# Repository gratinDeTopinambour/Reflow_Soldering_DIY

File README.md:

# Reflow Soldering DIY Controller

**Convert a standard consumer oven into a precise PCB reflow soldering station.**

This repository contains the complete electronics design, firmware, and mechanical files for a custom Reflow Oven Controller.The device is designed to precisely control a resistive heating element to follow the specific temperature profiles required for SMD soldering.

---

## 📂 Repository Structure

* **`Code/`**: Firmware source code for the STM32C0 microcontroller.
* **`Doc/`**: General project documentation and datasheets.
* **`Electronics/`**: Hardware design files, including the detailed technical rationale.
* **`3Dprint/`**: STL and CAD files for the controller enclosure.

---

## ⚡ System Overview

The controller operates as a closed-loop feedback system that regulates the temperature of a resistive heating element. 

### Key Technical Features
* **Power Control**: Designed for 220V / 50Hz mains up to **2400W** (12A design reference).
* **Switching Strategy**: Utilizes Zero-Crossing control to minimize EMI and power losses.
* **Galvanic Isolation**: Complete isolation between high-voltage AC and low-voltage logic via an Opto-TRIAC.
* **Microcontroller**: Powered by an **STM32C0 series** ARM Cortex-M0+.
* **User Interface**: Features an OLED display (128x64) and a 6-button navigation cluster.
* **Thermal Sensing**: Uses a glass-encapsulated NTC thermistor rated up to **300°C**.

---

## 🛠️ Hardware Specifications

The hardware design prioritizes low-cost, hand-solderable components and robust thermal management.

### Power Stage
| Component | Selection | Rationale |
| :--- | :--- | :--- |
| **TRIAC** | BTA16-600CW | 16A max current, snubberless design  |
| **Opto-TRIAC** | MOC3063M | Zero-crossing detection and safe isolation  |
| **Heatsink** | Boyd 530002B02500G | $2.6^{\circ}C/W$ resistance to handle ~13W dissipation  |

### Logic & Power
* **Input**: USB-C (5V).
* **Regulation**: L1117S33 LDO (SOT-223) provides a stable 3.3V rail for the MCU.
* **Optimization**: The temperature sensor uses an optimized $1.8k\Omega$ bridge resistor to maximize ADC voltage swing between $60^{\circ}C$ and $260^{\circ}C$.

---

## 🚀 Installation & Safety

### ⚠️ WARNING: High Voltage
This project involves **220V AC Mains**. Fatal injury or fire can occur if handled incorrectly. 
* Always ensure the device is unplugged before touching the electronics.
* Ensure the TRIAC heatsink is properly mounted as temperatures can reach $\approx 100^{\circ}C$ during operation.

### Setup
1. **Assembly**: Refer to the schematics in `Electronics/`. The design uses TSSOP-20 and SOT-223 packages for easy manual assembly.
2. **Firmware**: Flash the STM32C0 via the SWD interface pins (PA14/PA15).
3. **Calibration**: The system is tuned for a standard NTC thermistor (NRBG105F3950B1F).

---

## 👤 Author
**Valentin LEFEBVRE** (@topinambour)  
*Document Date: 06/02/2026*

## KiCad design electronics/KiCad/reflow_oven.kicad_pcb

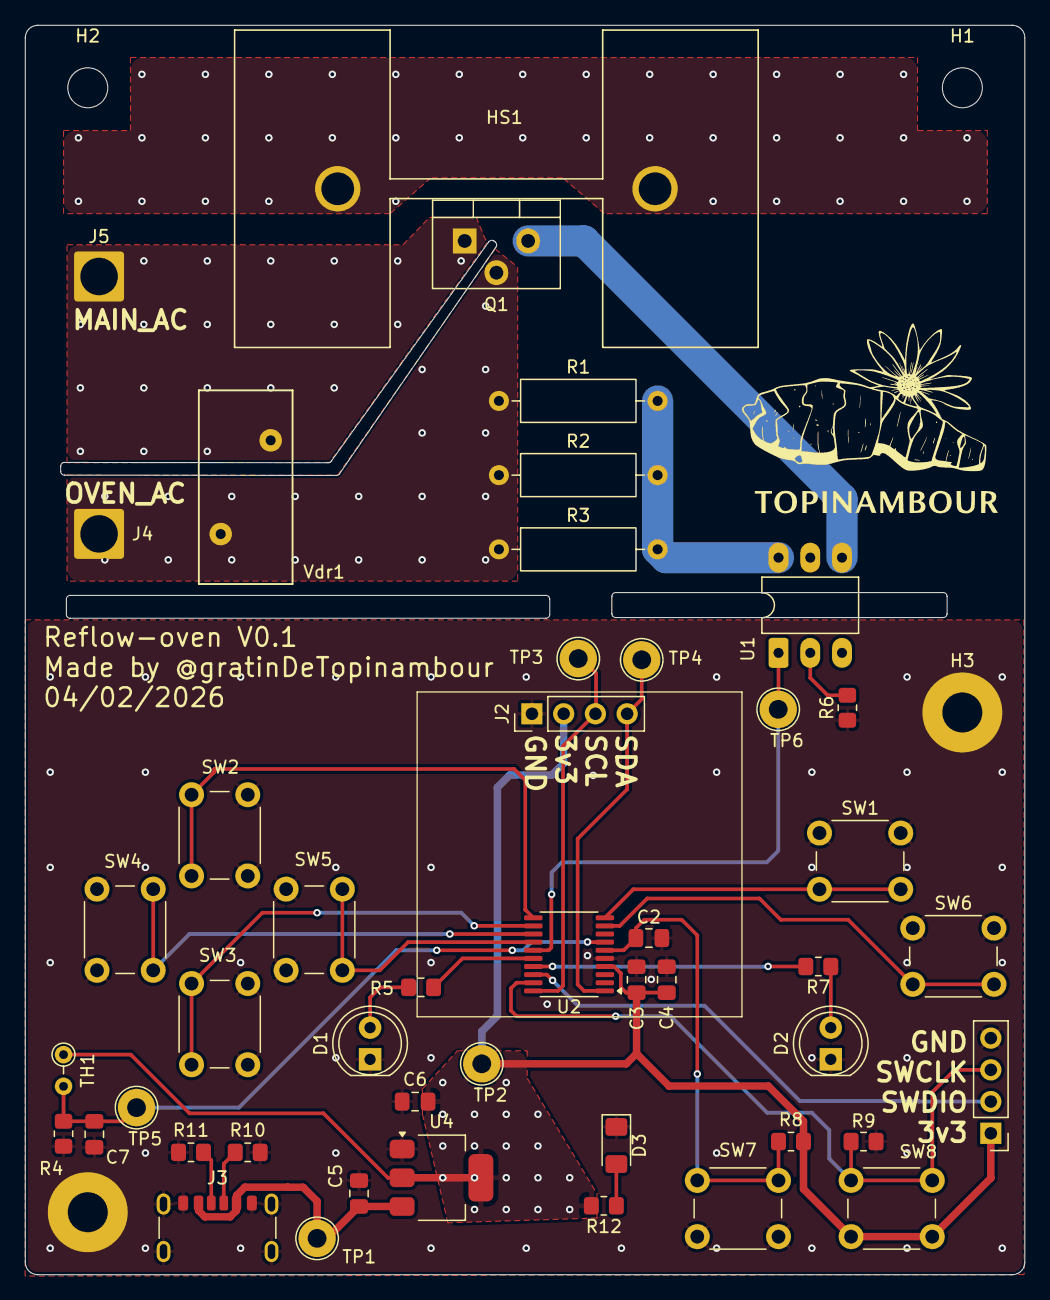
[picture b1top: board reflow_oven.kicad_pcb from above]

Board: 2 copper layers, 80.0 x 100.0 mm, 51 parts (0 on the bottom side), 29 nets.

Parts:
C2, C3, C7: 100nF; C_0805_2012Metric_Pad1.18x1.45mm_HandSolder
C4: 4.7uF; C_0805_2012Metric_Pad1.18x1.45mm_HandSolder
C5, C6: 10uF; C_0805_2012Metric_Pad1.18x1.45mm_HandSolder
D1: RED_LED; LED_D5.0mm
D2: GREEN_LED; LED_D5.0mm
D3: POWER_LED; LED_1206_3216Metric_Pad1.42x1.75mm_HandSolder
H1, H2: MountingHole; MountingHole_3.2mm_M3
H3, H4: MountingHole_Pad; MountingHole_3.2mm_M3_Pad
HS1: Heatsink; HEATSINK_530002B02500G
J1: Conn_01x04_Pin; PinHeader_1x04_P2.54mm_Vertical
J2: OLED_Display; PinHeader_1x04_P2.54mm_Vertical
J3: USB_C_Receptacle_PowerOnly_6P; USB_C_Receptacle_GCT_USB4125-xx-x-0190_6P_TopMnt_Horizontal
J4: Load_AC; SolderWire-2.5sqmm_1x01_D2.4mm_OD3.6mm
J5: Main_AC; SolderWire-2.5sqmm_1x01_D2.4mm_OD3.6mm
Q1: BTA16-600CW; TO-220-3_Vertical
R1, R2, R3: 1100; R_Axial_DIN0309_L9.0mm_D3.2mm_P12.70mm_Horizontal
R4: 1800; R_0805_2012Metric_Pad1.20x1.40mm_HandSolder
R5, R6, R7, R12: 150; R_0805_2012Metric_Pad1.20x1.40mm_HandSolder
R8, R9: 10k; R_0805_2012Metric_Pad1.20x1.40mm_HandSolder
R10, R11: 5.1k; R_0805_2012Metric_Pad1.20x1.40mm_HandSolder
SW1: Valid; SW_PUSH_6mm_H5mm
SW2: Up; SW_PUSH_6mm_H5mm
SW3: Down; SW_PUSH_6mm_H5mm
SW4: Left; SW_PUSH_6mm_H5mm
SW5: Right; SW_PUSH_6mm_H5mm
SW6: return; SW_PUSH_6mm_H5mm
SW7: NRST; SW_PUSH_6mm_H5mm
SW8: BOOT0; SW_PUSH_6mm_H5mm
TH1: Thermistor_NTC; R_Axial_DIN0204_L3.6mm_D1.6mm_P2.54mm_Vertical
TP1: 5v; TestPoint_Loop_D2.54mm_Drill1.5mm_Beaded
TP2: 3.3v; TestPoint_Loop_D2.54mm_Drill1.5mm_Beaded
TP3: I2C_SCL; TestPoint_Loop_D2.54mm_Drill1.5mm_Beaded
TP4: I2C_SDA; TestPoint_Loop_D2.54mm_Drill1.5mm_Beaded
TP5: Temp; TestPoint_Loop_D2.54mm_Drill1.5mm_Beaded
TP6: Pwr_cmd; TestPoint_Loop_D2.54mm_Drill1.5mm_Beaded
U1: MOC3063M; DIP-6_W7.62mm_LongPads
U2: STM32C011F6Px; TSSOP-20_4.4x6.5mm_P0.65mm
U4: LD1117S33TR_SOT223; SOT-223-3_TabPin2
Vdr1: S14K230; RV_Disc_D15.5mm_W7.5mm_P7.5mm

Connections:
+3.3V: C3.1, C4.1, C6.1, J1.1, J2.2, R8.1, R12.2, SW8.1, TH1.1, TP2.1, U2.4 (VDD), U4.2 (VO)
+5V: C5.1, J3.A9 (VBUS), J3.B9 (VBUS), TP1.1, U4.3 (VI)
/MICRO_CONTROLLER/NRST: C2.1, R8.2, SW7.2, U2.6 (PF2)
/MICRO_CONTROLLER/SWCLK/Boot0: J1.3, R9.1, SW8.2, U2.19 (PA14)
/MICRO_CONTROLLER/SWDIO: J1.2, U2.18 (PA13)
DISPLAY_SCL: J2.3, TP3.1, U2.20 (PB6)
DISPLAY_SDA: J2.4, TP4.1, U2.1 (PB7)
DOWN_INPUT: SW3.2, U2.12 (PA5)
GND: C2.2, C3.2, C4.2, C5.2, C6.2, C7.2, D1.1 (K), D2.1 (K), D3.1 (K), H3.1, H4.1, J1.4, J2.1, J3.A12 (GND), J3.B12 (GND), J3.S1 (SHIELD), R4.2, R6.1, R9.2, R10.2, R11.2, SW1.1, SW2.1, SW3.1, SW4.1, SW5.1, SW6.1, SW7.1, U2.5 (VSS), U4.1 (GND)
GREEN_LED: R7.2, U2.17 (PA10/PA12)
LEFT_INPUT: SW4.2, U2.13 (PA6)
Load_AC: J4.1, Q1.2 (A2), R1.1, R2.1, R3.1, Vdr1.1
Main_AC: J5.1, Q1.1 (A1), Vdr1.2
unnamed: D1.2 (A), R5.1
unnamed: D2.2 (A), R7.1
unnamed: D3.2 (A), R12.1
unnamed: HS1.1, HS1.2
unnamed: J3.A5 (CC1), R11.1
unnamed: J3.B5 (CC2), R10.1
unnamed: Q1.3 (G), U1.4
unnamed: R1.2, R2.2, R3.2, U1.6
unnamed: R6.2, U1.2
Power_CMD: TP6.1, U1.1, U2.15 (PA8)
RED_LED: R5.2, U2.16 (PA9/PA11)
RETURN_INPUT: SW6.2, U2.9 (PA2)
RIGHT_INPUT: SW5.2, U2.14 (PA7)
TEMP_ANA: C7.1, R4.1, TH1.2, TP5.1, U2.7 (PA0)
UP_INPUT: SW2.2, U2.11 (PA4)
VALID_INPUT: SW1.2, U2.10 (PA3)

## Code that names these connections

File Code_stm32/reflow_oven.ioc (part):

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Mcu.Name=STM32C011F(4-6)Px
Mcu.Package=TSSOP20
Mcu.UserName=STM32C011F6Px
PA0.Mode=IN0
PA0.Signal=ADC1_IN0
PA11\ [PA9].Signal=GPIO_Output
PA12\ [PA10].Signal=GPIO_Output
PA2.GPIOParameters=GPIO_PuPd
PA2.GPIO_PuPd=GPIO_PULLUP
PA2.Signal=GPIO_Input
PA3.GPIOParameters=GPIO_PuPd
PA3.GPIO_PuPd=GPIO_PULLUP
PA3.Signal=GPIO_Input
PA4.GPIOParameters=GPIO_PuPd
PA4.GPIO_PuPd=GPIO_PULLUP
PA4.Signal=GPIO_Input
PA5.GPIOParameters=GPIO_PuPd
PA5.GPIO_PuPd=GPIO_PULLUP
PA5.Signal=GPIO_Input
PA6.GPIOParameters=GPIO_PuPd
PA6.GPIO_PuPd=GPIO_PULLUP
PA6.Signal=GPIO_Input
PA7.GPIOParameters=GPIO_PuPd
PA7.GPIO_PuPd=GPIO_PULLUP
PA7.Signal=GPIO_Input
PA8.Signal=GPIO_Output
PB6.GPIOParameters=GPIO_Pu
PB6.GPIO_Pu=GPIO_PULLUP
PB6.Mode=I2C
PB6.Signal=I2C1_SCL
PB7.GPIOParameters=GPIO_Pu
PB7.GPIO_Pu=GPIO_PULLUP
PB7.Mode=I2C
PB7.Signal=I2C1_SDA
RCC.HSE_VALUE=8000000
RCC.SYSCLKFreq_VALUE=48000000
board=custom

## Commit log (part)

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2026-01-27 Create usefull_link
